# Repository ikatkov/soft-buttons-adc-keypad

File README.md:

# ADC based keypad

This is a 3-wires ADC based 3x3 keypad. Only 3 pins Vcc-GND-ADC.

Ideal to be used with salvaged silicon buttons from remote controls.
There is a momentary button under silicon cap.

# Code

```

enum KEYPAD_BUTTONS
{
    BTN_NOT_PRESSED, // 0
    BTN_TOP_LEFT,    // 1
    BTN_UP,          // 2
    BTN_TOP_RIGHT,   // 3
    BTN_LEFT,        // 4
    BTN_CENTER,      // 5
    BTN_RIGHT,       // 6
    BTN_BACK,        // 7
    BTN_DOWN,        // 8
    BTN_MENU         // 9
};
const char *buttonsNames[] = {"NOT PRESSED", "BTN_TOP_LEFT", "BTN_UP", "BTN_TOP_RIGHT", "BTN_LEFT", "BTN_CENTER", "BTN_RIGHT", "BTN_BACK", "BTN_DOWN", "BTN_MENU"};
KEYPAD_BUTTONS prev_button_pressed = BTN_NOT_PRESSED;

byte read_buttons()
{
    int voltage = analogRead(A0);
    KEYPAD_BUTTONS result = BTN_NOT_PRESSED;
    KEYPAD_BUTTONS new_button_pressed = BTN_NOT_PRESSED;
    if (voltage >= 540 && voltage <= 590) // 558
        new_button_pressed = BTN_MENU;
    else if (voltage >= 650 && voltage < 670) // 655
        new_button_pressed = BTN_DOWN;
    else if (voltage >= 800 && voltage <= 845) // 825
        new_button_pressed = BTN_BACK;
    else if (voltage >= 580 && voltage <= 615) // 596
        new_button_pressed = BTN_RIGHT;
    else if (voltage >= 700 && voltage <= 725) // 708
        new_button_pressed = BTN_CENTER;
    else if (voltage >= 890 && voltage <= 940) // 912
        new_button_pressed = BTN_LEFT;
    else if (voltage >= 620 && voltage <= 640) // 631
        new_button_pressed = BTN_TOP_RIGHT;
    else if (voltage >= 740 && voltage <= 775) // 759
        new_button_pressed = BTN_UP;
    else if (voltage >= 980 && voltage <= 1023) // 1000
        new_button_pressed = BTN_TOP_LEFT;

    if (new_button_pressed == BTN_NOT_PRESSED && prev_button_pressed != BTN_NOT_PRESSED)
    {
        // button was released
        result = prev_button_pressed;
        prev_button_pressed = BTN_NOT_PRESSED;
    }
    else if (new_button_pressed != BTN_NOT_PRESSED && prev_button_pressed == BTN_NOT_PRESSED)
    {
        // button was pressed
        prev_button_pressed = new_button_pressed;
    }
    return result;
}

...

void loop()
{
    byte command = read_buttons();
    if (command != BTN_NOT_PRESSED)
    {
    	...
	}
}

```

# Notes

Performance seems OK. 

One disadvantage is that you need to alter source code when real ADC values are captured.
Some buttons yeld ADC valus that are very close to each other. I'm concern about long-term reliability.
You need to poll the state periodically, but you don't need to debounce.

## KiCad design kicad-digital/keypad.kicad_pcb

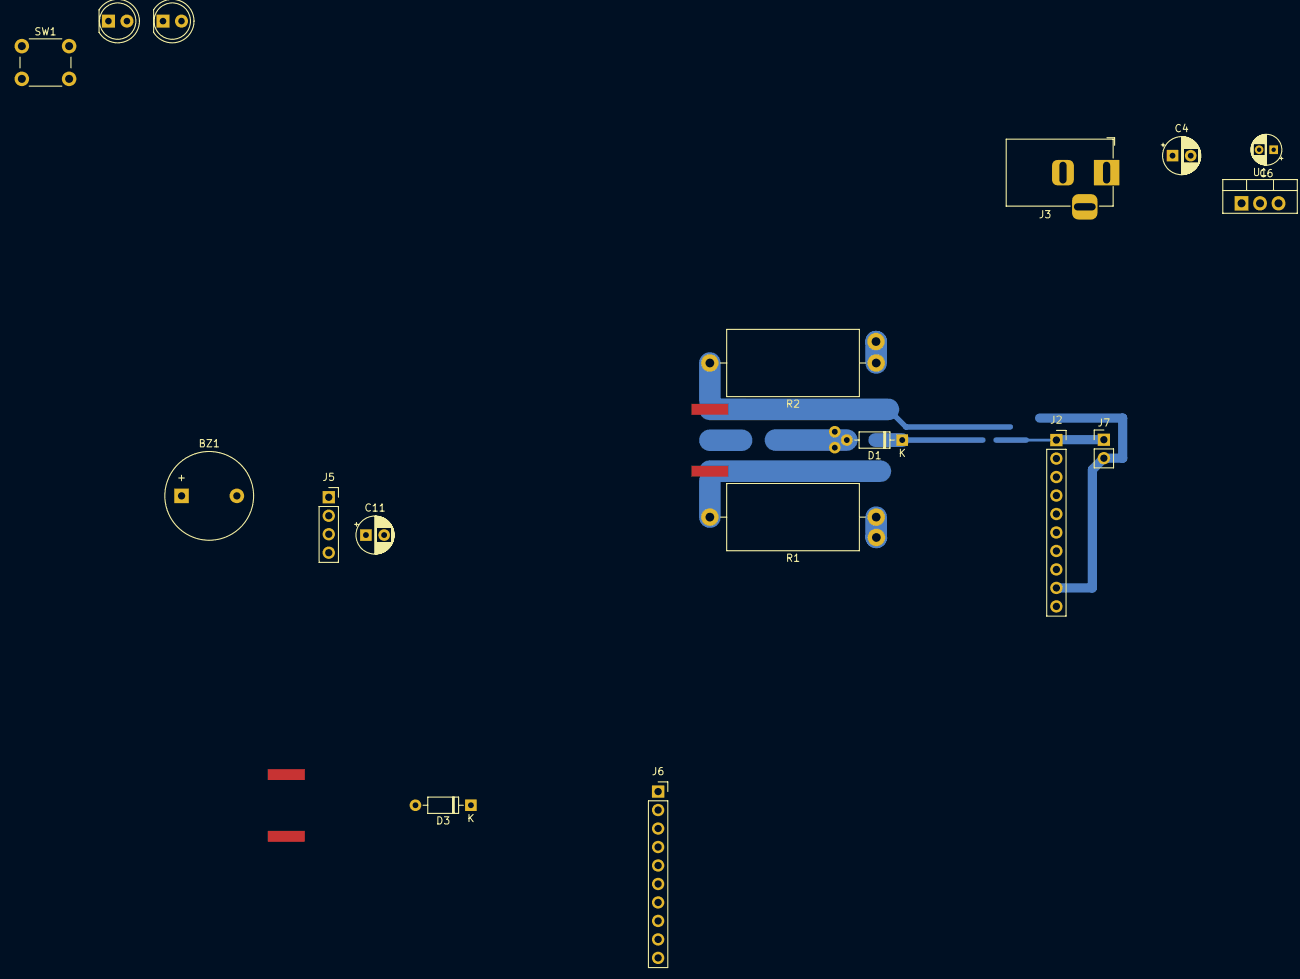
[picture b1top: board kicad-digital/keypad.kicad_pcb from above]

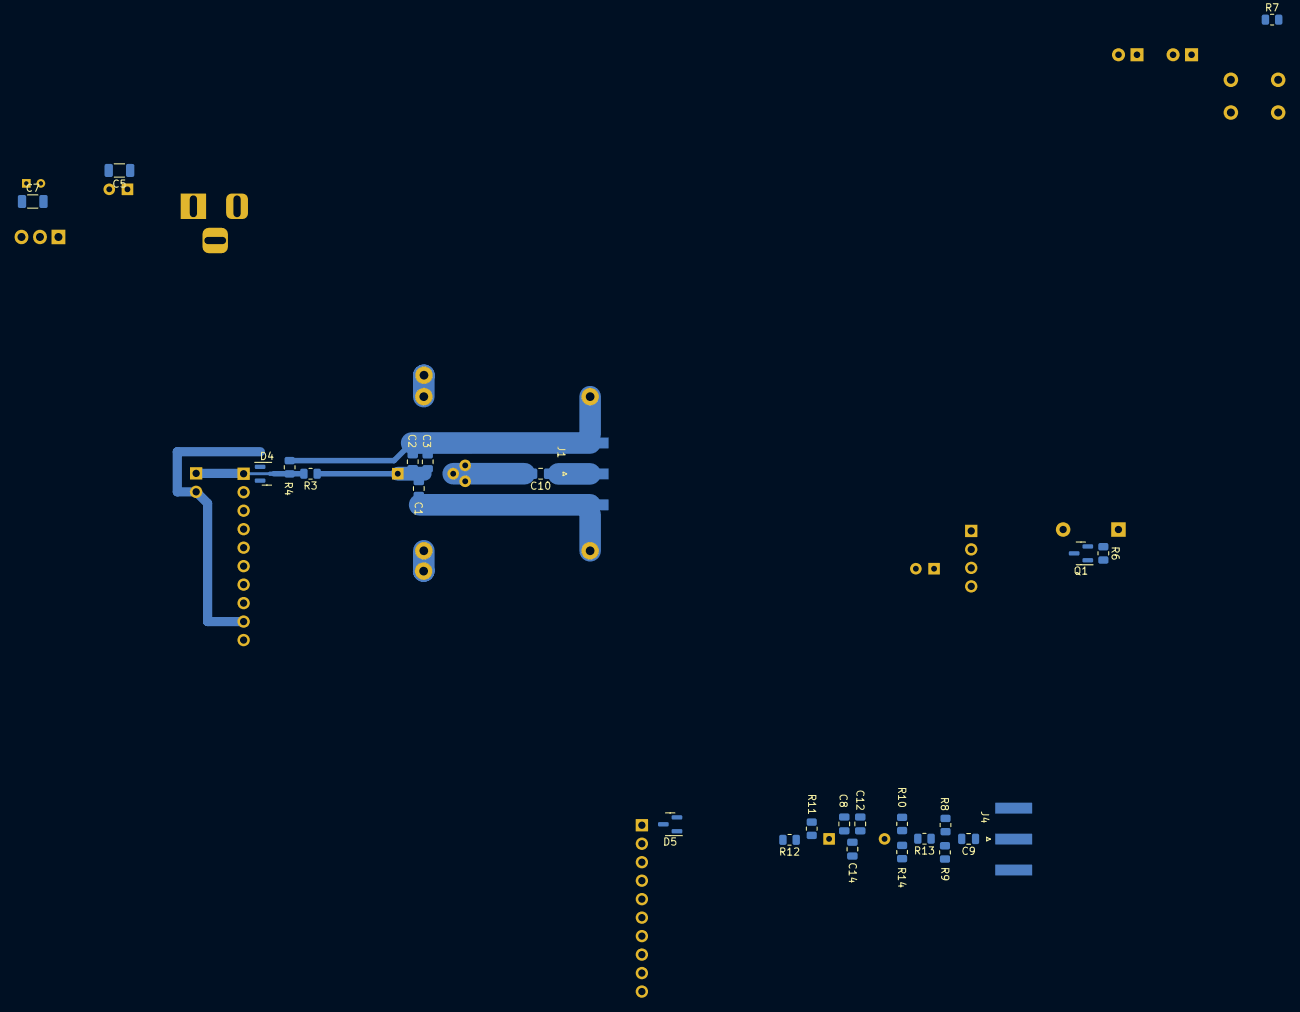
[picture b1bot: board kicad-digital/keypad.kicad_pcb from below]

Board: 4 copper layers, 43 parts (26 on the bottom side), 19 nets.

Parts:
BZ1: Buzzer; Buzzer_12x9.5RM7.6
C1, C14: 3.3n; C_0805_2012Metric
C2, C12: 100p; C_0805_2012Metric
C3, C8: 10p; C_0805_2012Metric
C4, C11: 100u; CP_Radial_D5.0mm_P2.50mm
C5, C7: 100n; C_1206_3216Metric
C6: 22u; CP_Radial_D4.0mm_P2.00mm
C9, C10: 15n; C_0805_2012Metric
D1, D3: 1N5711; D_DO-35_SOD27_P7.62mm_Horizontal
D2: HI_Port; LED_D5.0mm
D4, D5: BAT54S; SOT-23
D6: LO_Port; LED_D5.0mm
J1, J4: SMA; SMA_Amphenol_132289_EdgeMount
J2, J6: ADS1115; PinSocket_1x10_P2.54mm_Vertical
J3: Barrel_Jack; BarrelJack_Horizontal
J5: Display; PinSocket_1x04_P2.54mm_Vertical
J7: TestPoint; PinHeader_1x02_P2.54mm_Vertical
Q1: 2N3904; SOT-23
R1, R2: 100; R_Axial_DIN0918_L18.0mm_D9.0mm_P22.86mm_Horizontal
R3: 180k; R_0805_2012Metric
R4: 36k; R_0805_2012Metric
R6, R12: 1k; R_0805_2012Metric
R7: 3k; R_0805_2012Metric
R8: 620; R_0805_2012Metric
R9: 560; R_0805_2012Metric
R10: 91; R_0805_2012Metric
R11: 270k; R_0805_2012Metric
R13: 18; R_0805_2012Metric
R14: 82; R_0805_2012Metric
SW1: HI/LO port; SW_PUSH_6mm
U1: L7805; TO-220-3_Vertical

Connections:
+12V: C4.1, C5.1, J3.1, U1.1 (IN)
A3: D4.3 (COM), J2.1, J7.1, R3.2, R4.1
GND: C4.2, C5.2, C6.2, C7.2, D2.1 (K), D4.1 (A), D5.1 (A), J2.9, J3.2, J5.1, J7.2, Q1.2 (E), SW1.2, U1.2 (GND)
GNDA: C1.2, C2.2, C3.2, C8.1, J1.2 (Ext), R1.2, R2.2, R4.2, R9.1, R10.1
unnamed: BZ1.2 (+), Q1.3 (C)
unnamed: C9.2, R8.1, R9.2, R13.1
unnamed: C10.2, D1.2 (A), R1.1, R2.1
unnamed: C1.1, C2.1, C3.1, D1.1 (K), R3.1
unnamed: D2.2 (A), D6.1 (K), R7.2
unnamed: D3.2 (A), R10.2, R13.2, R14.1
unnamed: C8.2, C12.1, C14.1, D3.1 (K), R11.1, R12.1
unnamed: D5.3 (COM), R12.2
unnamed: C10.1, J1.1 (In)
unnamed: C12.2, C14.2, J4.2 (Ext), R8.2, R11.2, R14.2
unnamed: C9.1, J4.1 (In)
unnamed: Q1.1 (B), R6.2
SDA: J2.7, J5.3
SLC: J2.8, J5.4
VCC: BZ1.1 (-), C6.1, C7.1, D4.2 (K), D5.2 (K), D6.2 (A), J2.10, J5.2, U1.3 (OUT)

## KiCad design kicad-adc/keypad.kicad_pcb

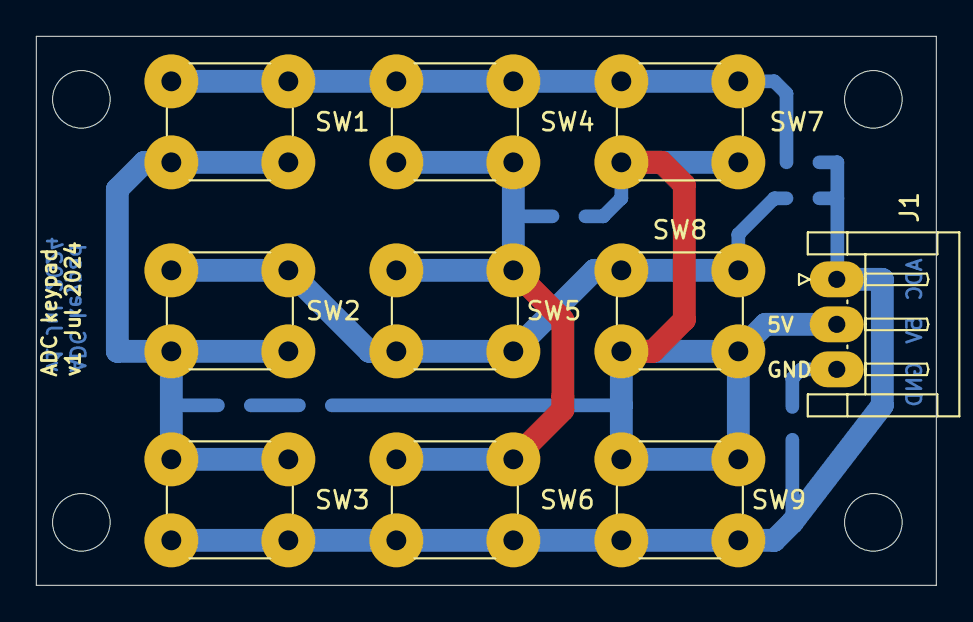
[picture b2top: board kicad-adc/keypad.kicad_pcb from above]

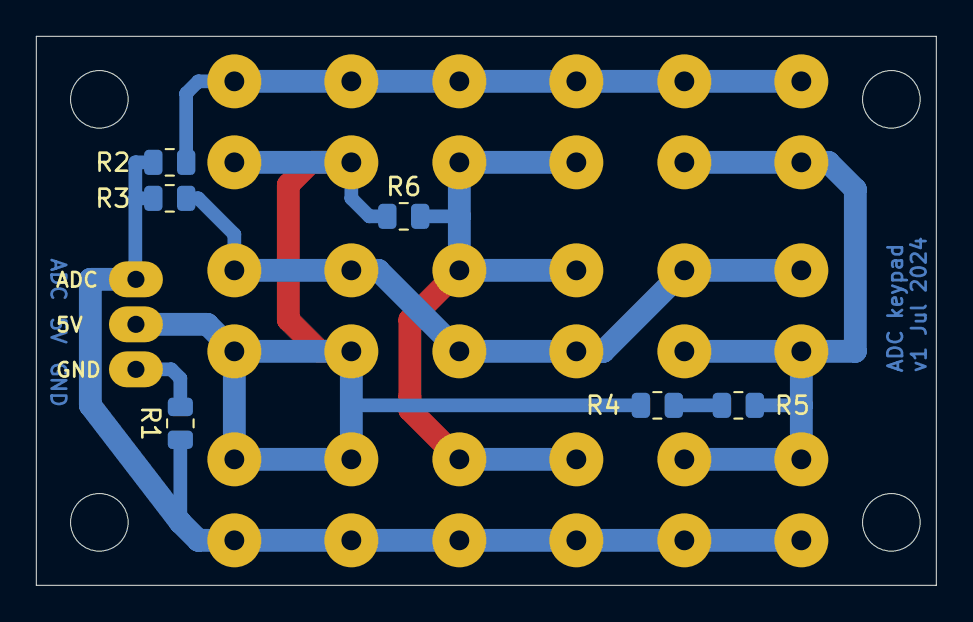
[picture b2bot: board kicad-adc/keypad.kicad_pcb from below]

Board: 4 copper layers, 50.0 x 30.5 mm, 20 parts (6 on the bottom side), 8 nets.

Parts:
H1, H2, H3, H4: MountingHole; MountingHole_3.2mm_M3
J1: Conn; JST_EH_S3B-EH_1x03_P2.50mm_Horizontal
R1: 10k; R_0805_2012Metric
R2, R5: 2.2k; R_0805_2012Metric
R3: 1k; R_0805_2012Metric
R4: 3.9k; R_0805_2012Metric
R6: 3.3k; R_0805_2012Metric
SW1, SW2, SW3, SW4, SW5, SW6, SW7, SW8, SW9: B1; SW_PUSH_6mm

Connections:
+5V: J1.2, R4.1, R6.1, SW7.2, SW8.2, SW9.2
ADC: J1.1, R1.1, R2.2, R3.2, SW3.1, SW6.1, SW9.1
GND: J1.3, R1.2
unnamed: R2.1, SW1.1, SW4.1, SW7.1
unnamed: R3.1, SW2.1, SW5.1, SW8.1
unnamed: R4.2, R5.1
unnamed: R5.2, SW1.2, SW2.2, SW3.2
unnamed: R6.2, SW4.2, SW5.2, SW6.2
